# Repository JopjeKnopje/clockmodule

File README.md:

# Clock Module

The idea behind this project is to have a standalone clock circuit to debug ICs at a very low clock speed.

It is mainly inspired by [Ben Eater's](https://eater.net/8bit/clock) version.

### Features
- Manual pulse Mode.
- Variable frequency clock.
- DC Input Jack 7v - 15v @ approx. 100mA.
- Raw 5v power in for breadboard compatability.
- Lots of LEDs :)

### Parts
- 2x 0.01uF - Ceramic Capacitor
- 2x 4.7uF - Capacitor
- 1x 470uF - Capacitor
- 1x .33uF - Ceramic Capacitor
- 4x .1uF - Ceramic Capacitor
- 1x 1uF - Capacitor
- 1x 1N4007 - Diode
- 4x 5mm LED
- 2x 01x02 Female Pin header
- 1x DC Jack
- 6x 1K - Resistor
- 2x 51K - Resistor
- 2x 10K - Resistor
- 1x 100K - Potentiometer linear
- 2x Button
- 3x NE555P
- 1x L7805
- 1x 7400

### What does it look like
#### KiCad Render

### Todo
- [ ] Use CMOS ICs for a 5vpp output
- [x] Add partslist
- [ ] Add photos
- [x] Swap silkscreen position of c3 and c4 
- [x] Different footprint for c8

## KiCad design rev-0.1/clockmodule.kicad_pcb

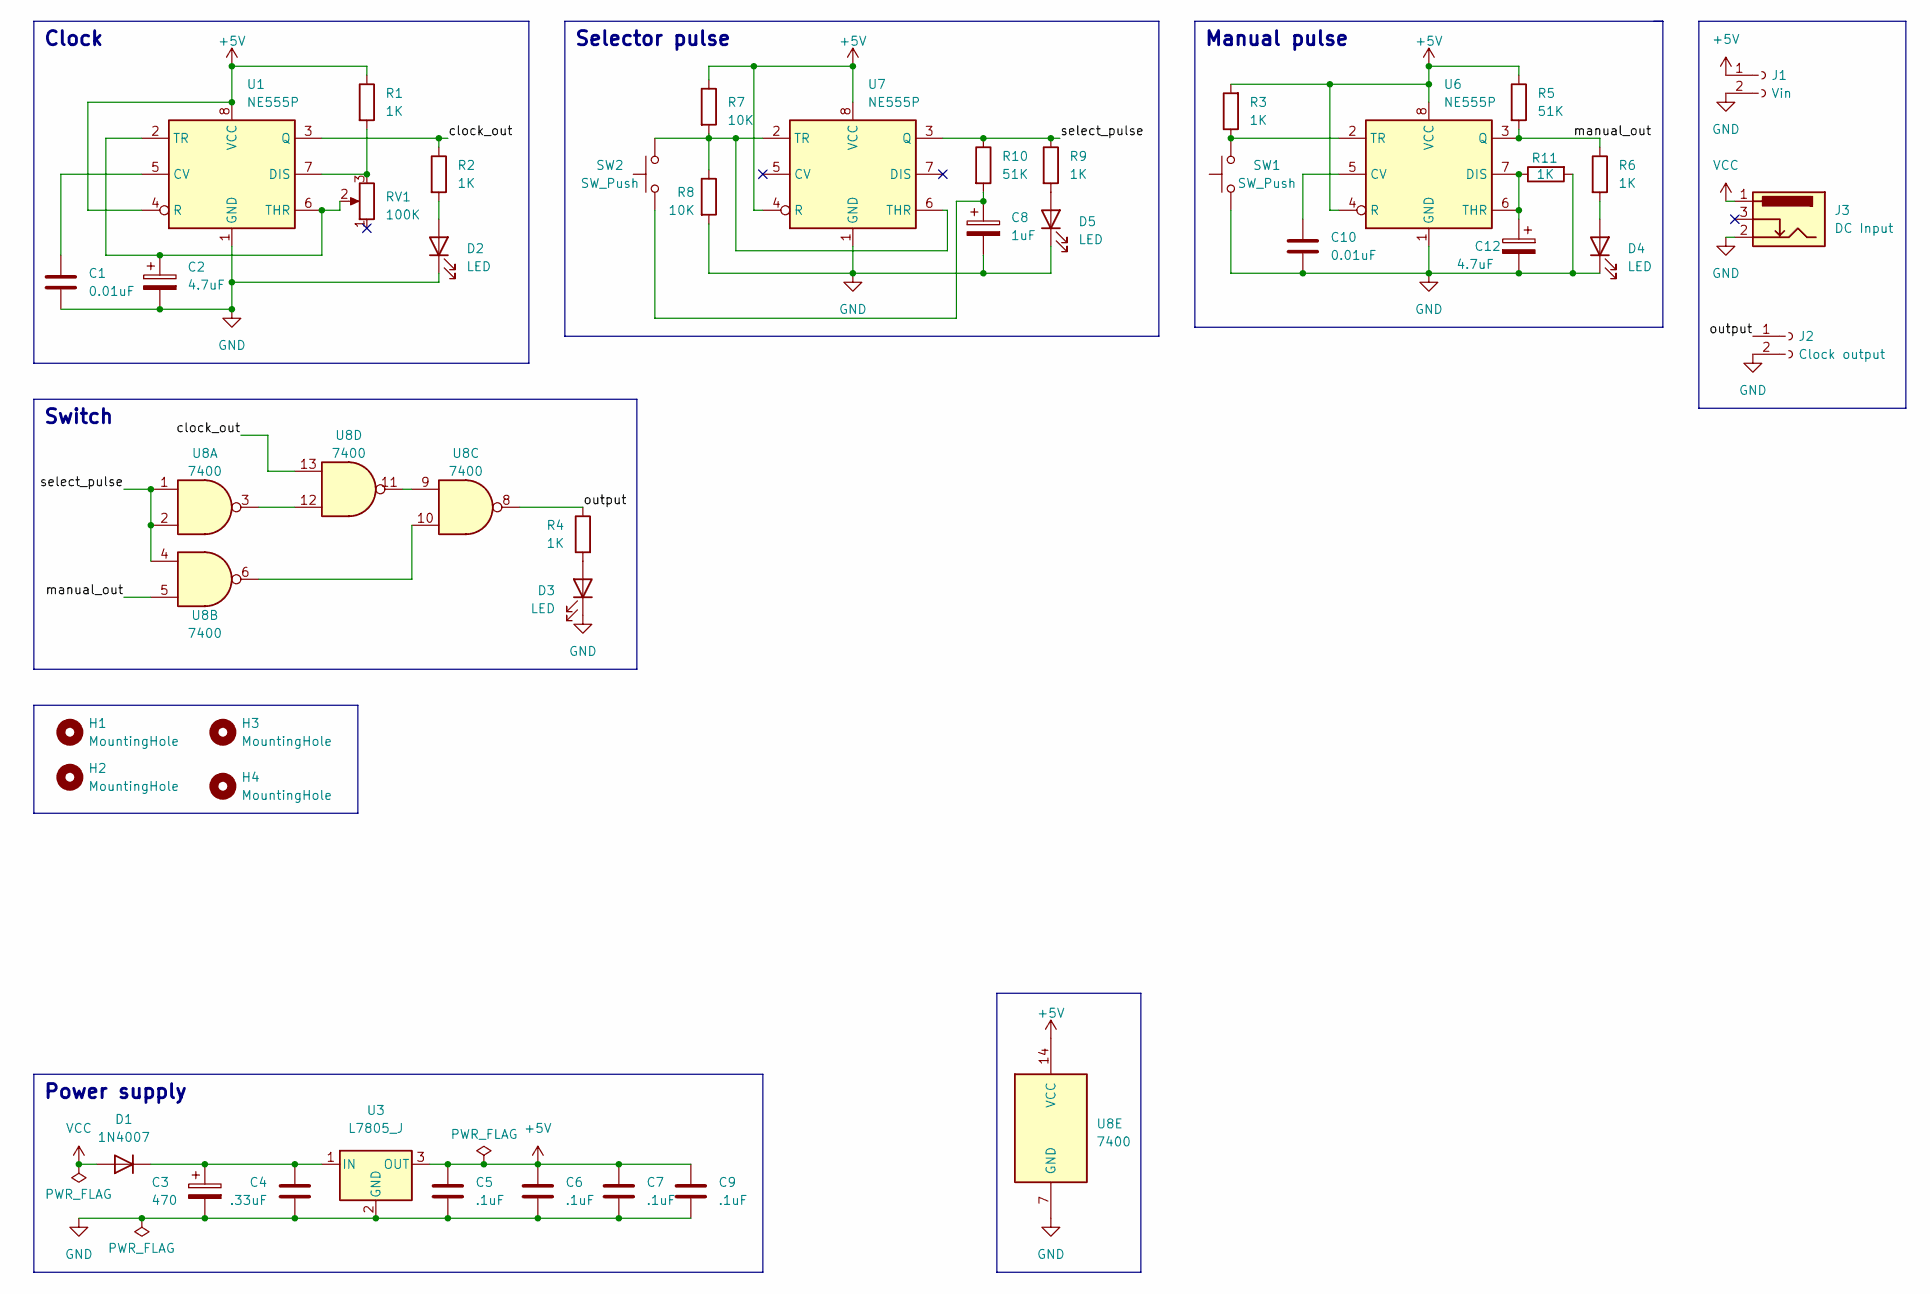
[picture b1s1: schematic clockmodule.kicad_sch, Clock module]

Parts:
C1, C10: 0.01uF; C_Disc_D3.0mm_W1.6mm_P2.50mm
C2, C12: 4.7uF; CP_Radial_D4.0mm_P1.50mm
C3: 470; CP_Radial_D6.3mm_P2.50mm
C4: .33uF; C_Disc_D3.0mm_W1.6mm_P2.50mm
C5, C6, C7, C9: .1uF; C_Disc_D3.0mm_W1.6mm_P2.50mm
C8: 1uF; CP_Radial_D4.0mm_P1.50mm
D1: 1N4007; D_DO-41_SOD81_P7.62mm_Horizontal
D2, D3, D4, D5: LED; LED_D5.0mm
H1, H2, H3, H4: MountingHole; MountingHole_4.3mm_M4
J1: Vin; PinSocket_1x02_P2.54mm_Vertical
J2: Clock output; PinSocket_1x02_P2.54mm_Vertical
J3: DC Input; BarrelJack_GCT_DCJ200-10-A_Horizontal
R1, R2, R3, R4, R6, R9, R11: 1K; R_Axial_DIN0204_L3.6mm_D1.6mm_P7.62mm_Horizontal
R5, R10: 51K; R_Axial_DIN0204_L3.6mm_D1.6mm_P7.62mm_Horizontal
R7, R8: 10K; R_Axial_DIN0204_L3.6mm_D1.6mm_P7.62mm_Horizontal
RV1: 100K; trimmer_alps-rk09k1130ah1
SW1, SW2: SW_Push; SW_PUSH_6mm_H5mm
U1, U6, U7: NE555P; DIP-8_W7.62mm
U3: L7805_J; TO-220-3_Horizontal_TabDown
U8: 7400; DIP-14_W7.62mm

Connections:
+5V: C5.1, C6.1, C7.1, C9.1, J1.1, R1.1, R3.2, R5.1, R7.1, U1.4 (R), U1.8 (VCC), U3.3 (OUT), U6.4 (R), U6.8 (VCC), U7.4 (R), U7.8 (VCC), U8.14 (VCC)
/clock_out: R2.1, U1.3 (Q), U8.13
/manual_out: R5.2, R6.1, U6.3 (Q), U8.5
/output: J2.1, R4.1, U8.8
/select_pulse: R9.1, R10.1, U7.3 (Q), U8.1, U8.2, U8.4
GND: C1.1, C2.2, C3.2, C4.1, C5.2, C6.2, C7.2, C8.2, C9.2, C10.2, C12.2, D2.1 (K), D3.1 (K), D4.1 (K), D5.1 (K), J1.2, J2.2, J3.2, R8.2, R11.2, SW1.2, U1.1 (GND), U3.2 (GND), U6.1 (GND), U7.1 (GND), U8.7 (GND)
unnamed: C8.1, R10.2, SW2.2
unnamed: C3.1, C4.2, D1.1 (K), U3.1 (IN)
unnamed: D2.2 (A), R2.2
unnamed: D3.2 (A), R4.2
unnamed: D4.2 (A), R6.2
unnamed: D5.2 (A), R9.2
unnamed: C1.2, U1.5 (CV)
unnamed: R1.2, RV1.3, U1.7 (DIS)
unnamed: C2.1, RV1.2, U1.2 (TR), U1.6 (THR)
unnamed: C10.1, U6.5 (CV)
unnamed: C12.1, R11.1, U6.6 (THR), U6.7 (DIS)
unnamed: R3.1, SW1.1, U6.2 (TR)
unnamed: R7.2, R8.1, SW2.1, U7.2 (TR), U7.6 (THR)
unnamed: U8.6, U8.10
unnamed: U8.9, U8.11
unnamed: U8.3, U8.12
VCC: D1.2 (A), J3.1

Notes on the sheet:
Power supply
Selector pulse
Switch
Clock
Manual pulse

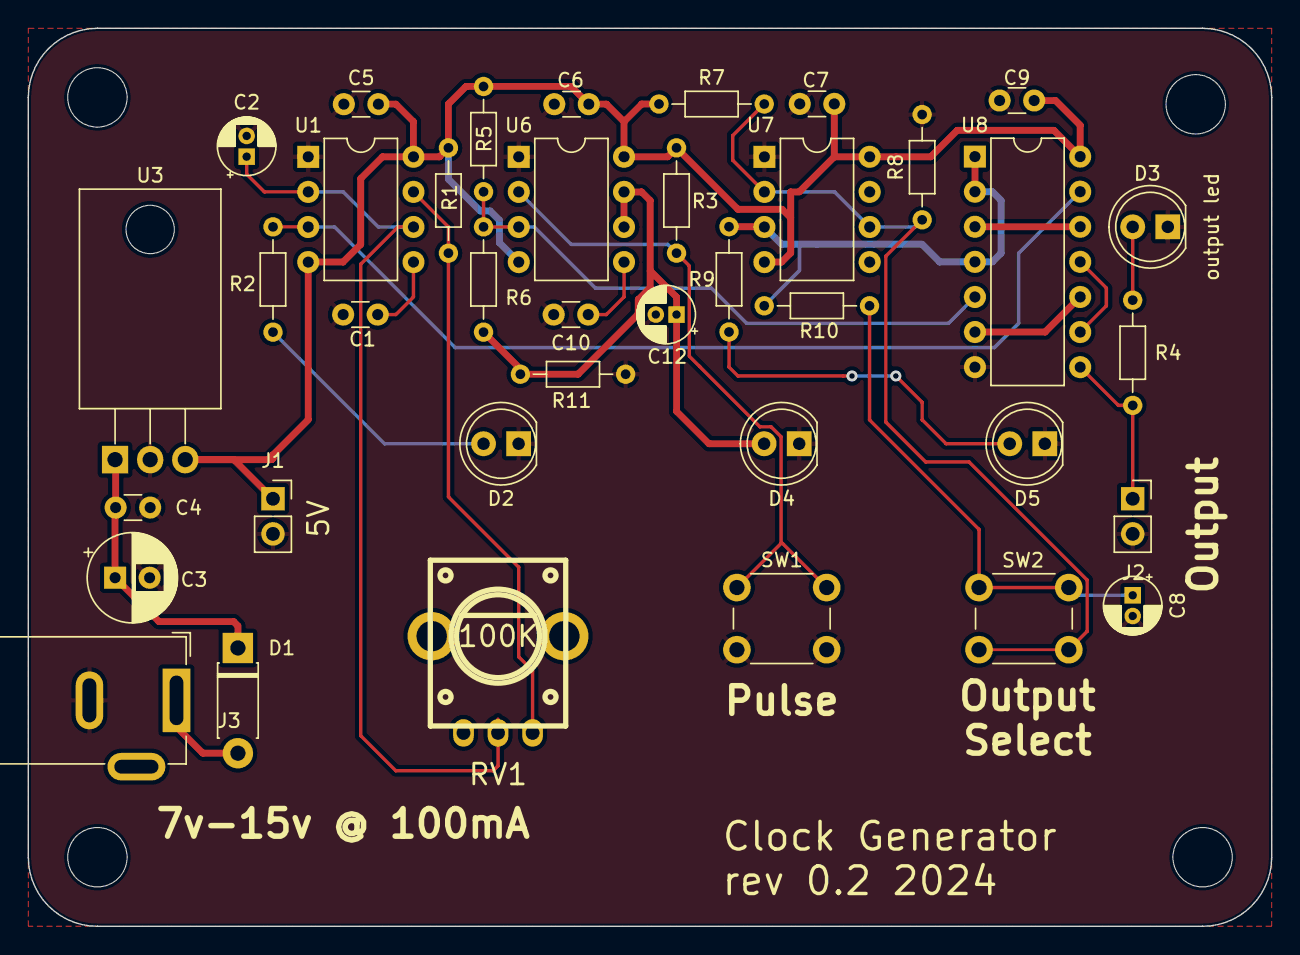
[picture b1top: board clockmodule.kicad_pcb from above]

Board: 2 copper layers, 90.0 x 65.0 mm, 42 parts (0 on the bottom side), 23 nets.

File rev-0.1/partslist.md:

- 2x 0.01uF, C
- 2x 4.7uF, C_Polarized
- 1x 470, C_Polarized
- 1x .33uF, C
- 4x .1uF, C
- 1x 1uF, C_Polarized
- 1x 1N4007, D
- 4x LED, LED
- 4x MountingHole, MountingHole
- 1x Vin, Conn_01x02_Female
- 1x Clock output, Conn_01x02_Female
- 1x DC Input, Barrel_Jack_Switch
- 6x 1K, R
- 2x 51K, R
- 2x 10K, R
- 1x 100K, R_Potentiometer
- 2x SW_Push, SW_Push
- 3x NE555P, NE555P
- 1x L7805_J, L7805_J
- 1x 7400, 7400

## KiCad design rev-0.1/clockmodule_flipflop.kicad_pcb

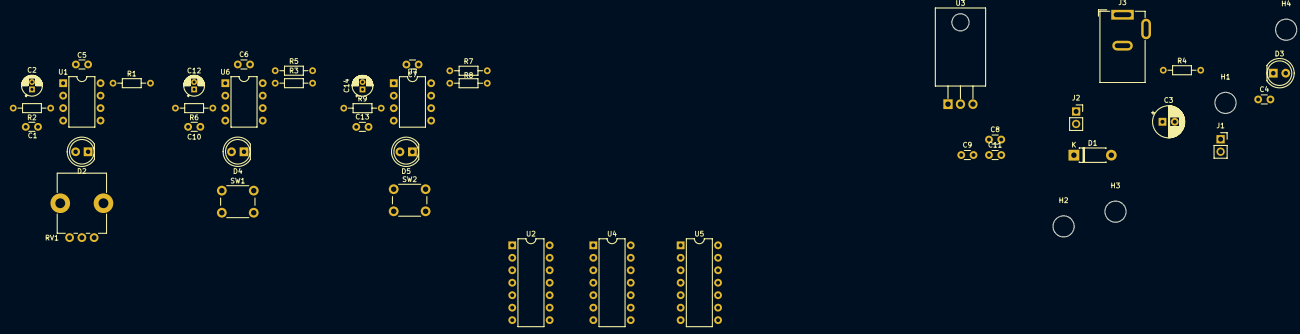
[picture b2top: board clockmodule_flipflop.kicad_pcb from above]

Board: 2 copper layers, 45 parts (0 on the bottom side), 25 nets, no tracks yet.

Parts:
C1, C10, C13: 0.01uF; C_Disc_D3.0mm_W1.6mm_P2.50mm
C2, C12, C14: 4.7uF; CP_Radial_D4.0mm_P1.50mm
C3: 470; CP_Radial_D6.3mm_P2.50mm
C4: .33uF; C_Disc_D3.0mm_W1.6mm_P2.50mm
C5, C6, C7, C8, C9, C11: .1uF; C_Disc_D3.0mm_W1.6mm_P2.50mm
D1: 1N4007; D_DO-41_SOD81_P7.62mm_Horizontal
D2, D3, D4, D5: LED; LED_D5.0mm
H1, H2, H3, H4: MountingHole; MountingHole_4.3mm_M4
J1, J2: Conn_01x02_Female; PinSocket_1x02_P2.54mm_Vertical
J3: Barrel_Jack_Switch; BarrelJack_GCT_DCJ200-10-A_Horizontal
R1, R2, R3, R4, R6, R7, R9: 1K; R_Axial_DIN0204_L3.6mm_D1.6mm_P7.62mm_Horizontal
R5, R8: 51K; R_Axial_DIN0204_L3.6mm_D1.6mm_P7.62mm_Horizontal
RV1: 100K; Potentiometer_Alps_RK09K_Single_Vertical
SW1, SW2: SW_Push; SW_PUSH_6mm_H5mm
U1, U6, U7: NE555P; DIP-8_W7.62mm
U2: 74LS107; DIP-14_W7.62mm
U3: L7805_J; TO-220-3_Horizontal_TabDown
U4: 74LS08; DIP-14_W7.62mm
U5: 74HC86; DIP-14_W7.62mm

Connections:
+5V: C5.1, C6.1, C7.1, C8.1, C9.1, C11.1, J1.1, R1.1, R3.2, R5.1, R7.2, R8.1, U1.4 (R), U1.8 (VCC), U2.1 (J), U2.4 (K), U2.13 (~R), U2.14 (VCC), U3.3 (OUT), U4.14 (VCC), U5.14 (VCC), U6.4 (R), U6.8 (VCC), U7.4 (R), U7.8 (VCC)
/clock_out: R2.1, U1.3 (Q), U4.2
/manual_out: R5.2, R6.1, U4.4, U6.3 (Q)
/output: D3.2 (A), J2.1, U5.3
/select_pulse: R8.2, R9.1, U2.12 (C), U7.3 (Q)
GND: C1.1, C2.2, C3.2, C4.1, C5.2, C6.2, C7.2, C8.2, C9.2, C10.2, C11.2, C12.2, C13.2, C14.2, D2.1 (K), D4.1 (K), D5.1 (K), J1.2, J2.2, J3.2, R4.2, SW1.2, SW2.2, U1.1 (GND), U2.7 (GND), U3.2 (GND), U4.7 (GND), U5.7 (GND), U6.1 (GND), U7.1 (GND)
unnamed: C3.1, C4.2, D1.1 (K), U3.1 (IN)
unnamed: D2.2 (A), R2.2
unnamed: D3.1 (K), R4.1
unnamed: D4.2 (A), R6.2
unnamed: D5.2 (A), R9.2
unnamed: C1.2, U1.5 (CV)
unnamed: R1.2, RV1.1, U1.7 (DIS)
unnamed: C2.1, RV1.2, U1.2 (TR), U1.6 (THR)
unnamed: U2.3 (Q), U4.5
unnamed: U2.2 (~Q), U4.1
unnamed: U4.3, U5.2
unnamed: U4.6, U5.1
unnamed: C10.1, U6.5 (CV)
unnamed: C12.1, U6.6 (THR), U6.7 (DIS)
unnamed: R3.1, SW1.1, U6.2 (TR)
unnamed: C13.1, U7.5 (CV)
unnamed: C14.1, U7.6 (THR), U7.7 (DIS)
unnamed: R7.1, SW2.1, U7.2 (TR)
VCC: D1.2 (A), J3.1

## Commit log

2022-03-29 Added README.md
2022-03-29 forgot to add project file
2022-03-30 added render
2022-03-30 added bomreader
2022-04-12 moved to rev-.1 folder
2022-04-12 changed README
2022-04-12 moved pics/
2022-04-12 README.md
2024-08-06 Swapped C4 and C3 silkscreen text
2024-08-06 Moved `R11`
2024-08-06 Change `C8` footprint
